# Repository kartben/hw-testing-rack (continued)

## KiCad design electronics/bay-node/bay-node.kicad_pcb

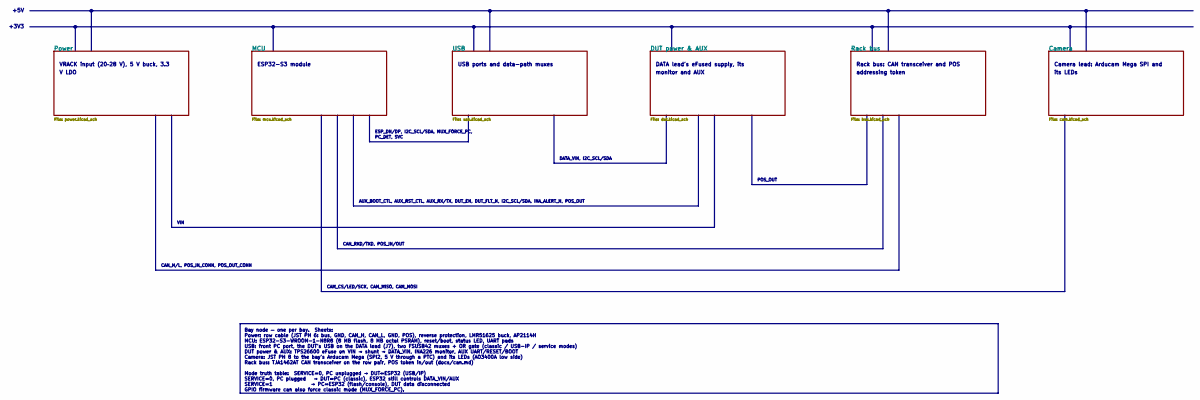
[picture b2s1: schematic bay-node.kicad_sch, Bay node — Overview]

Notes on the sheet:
VRACK input (20–28 V), 5 V buck, 3.3
V LDO
ESP32-S3 module
USB ports and data-path muxes
DATA lead's eFused supply, its
monitor and AUX
Rack bus: CAN transceiver and POS
addressing token
Camera lead: Arducam Mega SPI and
its LEDs
+3V3
+5V
ESP_DN/DP, I2C_SCL/SDA, MUX_FORCE_PC,
PC_DET, SVC
DATA_VIN, I2C_SCL/SDA
POS_OUT
AUX_BOOT_CTL, AUX_RST_CTL, AUX_RX/TX, DUT_EN, DUT_FLT_N, I2C_SCL/SDA, INA_ALERT_N, POS_OUT
VIN
CAN_RXD/TXD, POS_IN/OUT
CAN_H/L, POS_IN_CONN, POS_OUT_CONN
CAM_CS/LED/SCK, CAM_MISO, CAM_MOSI
Bay node — one per bay. Sheets: Power: row cable (JST PH 6: bus, GND, CAN_H, CAN_L, GND, POS), reverse protection, LMR51625 buck, AP2114H MCU: ESP32-S3-WROOM-1-N8R8 (8 MB flash, 8 MB octal PSRAM), reset/boot, status LED, UART pads USB: front PC port, the DUT's USB on the DATA lead (J7), two FSUSB42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

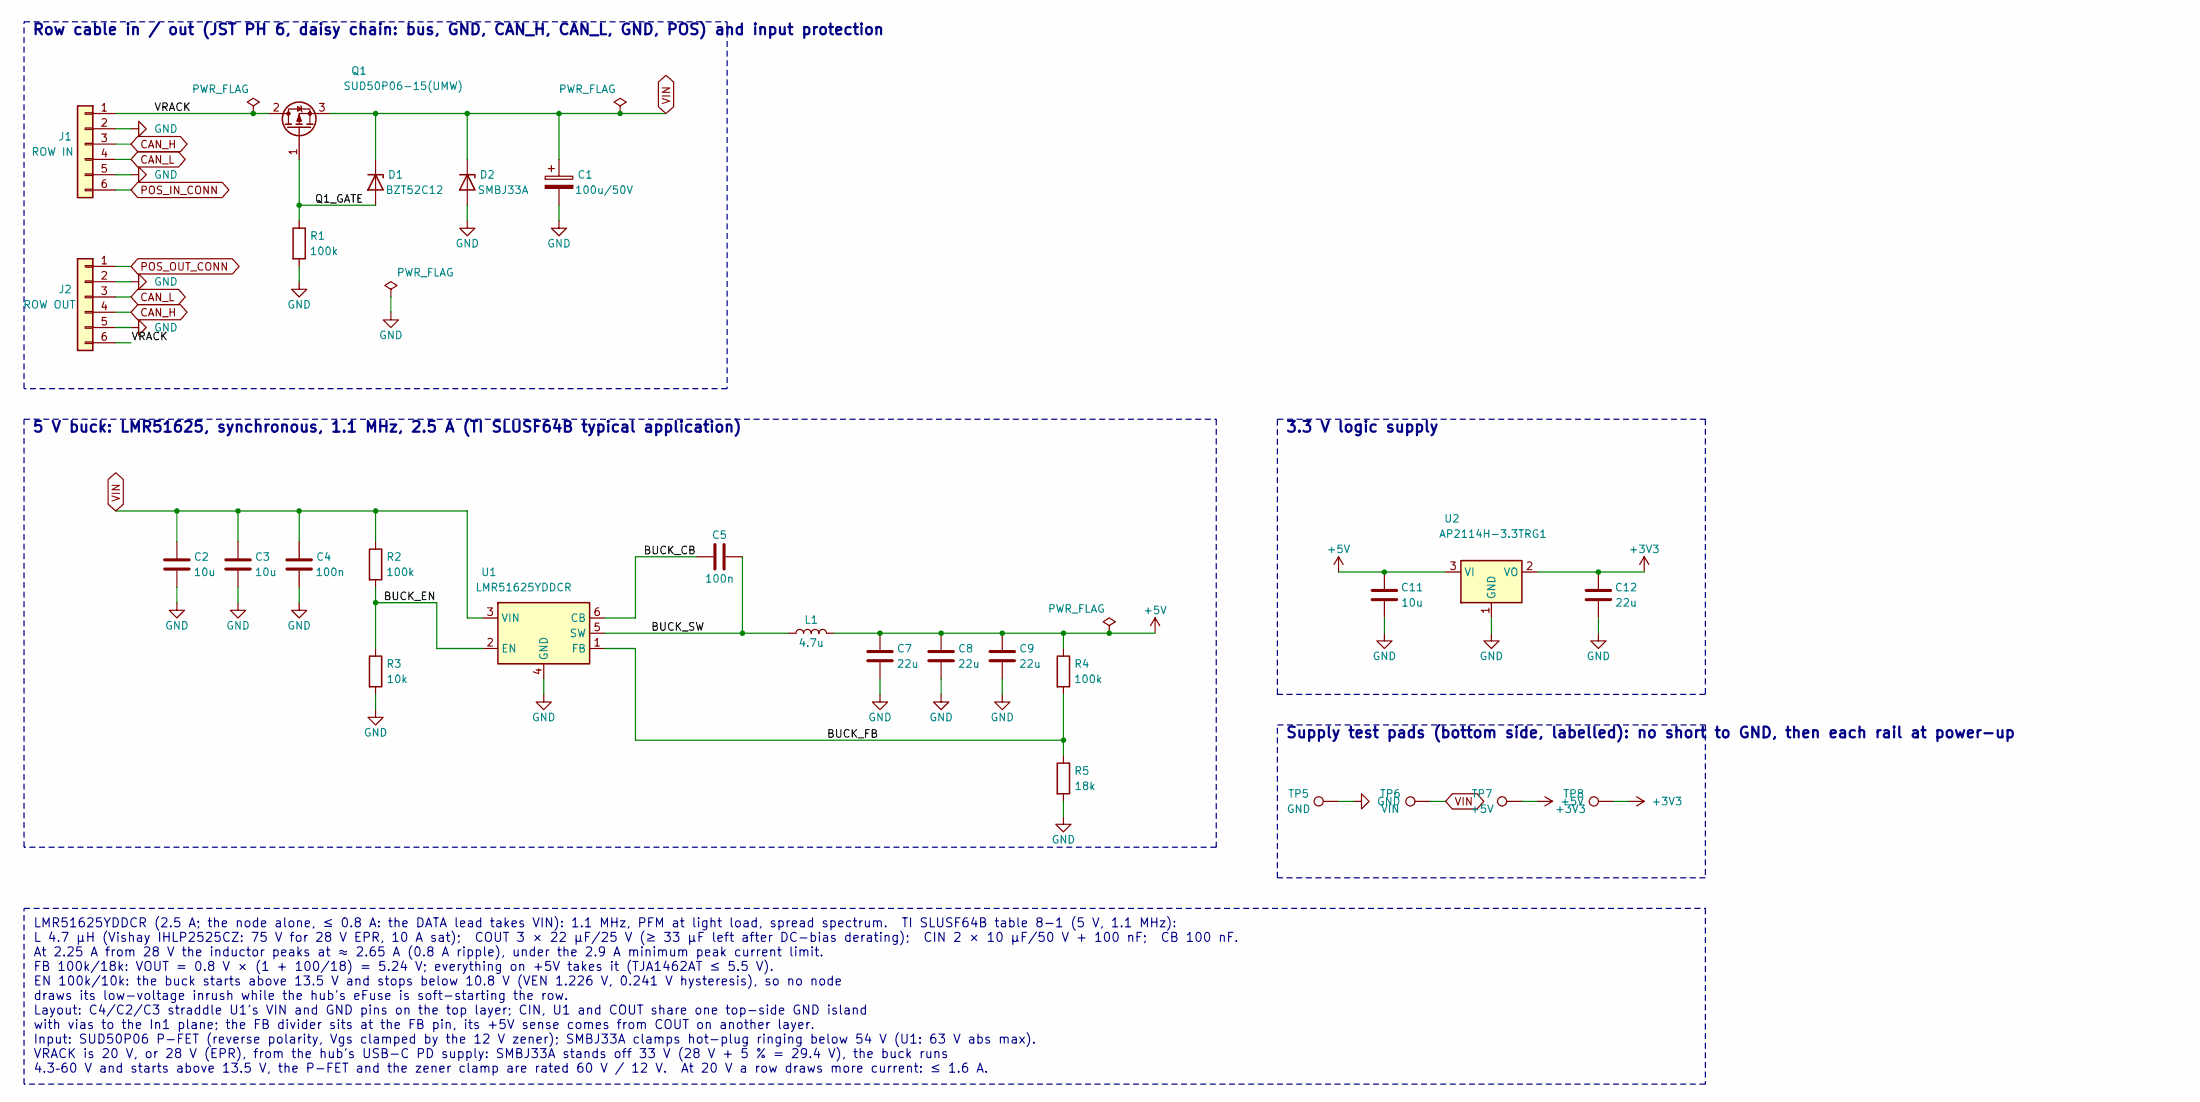
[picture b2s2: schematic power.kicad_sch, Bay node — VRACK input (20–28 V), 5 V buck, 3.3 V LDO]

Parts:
C1: 100u/50V; CP_Elec_8x10; MPN RVT1H101M0810; LCSC C3352
C2, C3: 10u; C_1206_3216Metric; MPN CL31A106KBHNNNE; LCSC C13585
C4, C5: 100n; C_0603_1608Metric; MPN CC0603KRX7R9BB104; LCSC C14663
C7, C8, C9, C12: 22u; C_1206_3216Metric; MPN CL31A226KAHNNNE; LCSC C12891
C11: 10u; C_0805_2012Metric; MPN CL21A106KAYNNNE; LCSC C15850
D1: BZT52C12; D_SOD-123; MPN BZT52C12; LCSC C43491
D2: SMBJ33A; D_SMB; MPN SMBJ33A; LCSC C78419
J1: ROW IN; JST_PH_S6B-PH-SM4-TB_1x06-1MP_P2.00mm_Horizontal; MPN S6B-PH-SM4-TB(LF)(SN); LCSC C265405
J2: ROW OUT; JST_PH_S6B-PH-SM4-TB_1x06-1MP_P2.00mm_Horizontal; MPN S6B-PH-SM4-TB(LF)(SN); LCSC C265405
L1: 4.7u; L_Changjiang_FXL0630; MPN IHLP2525CZEK4R7M01; LCSC C48009678
Q1: SUD50P06-15(UMW); TO-252-2; MPN SUD50P06-15(UMW); LCSC C7503186
R1, R2, R4: 100k; R_0603_1608Metric; MPN 0603WAF1003T5E; LCSC C25803
R3: 10k; R_0603_1608Metric; MPN 0603WAF1002T5E; LCSC C25804
R5: 18k; R_0603_1608Metric; MPN 0603WAF1802T5E; LCSC C25810
TP5: GND; TestPoint_Pad_D1.5mm; MPN test pad
TP6: VIN; TestPoint_Pad_D1.5mm; MPN test pad
TP7: +5V; TestPoint_Pad_D1.5mm; MPN test pad
TP8: +3V3; TestPoint_Pad_D1.5mm; MPN test pad
U1: LMR51625YDDCR; TSOT-23-6; MPN LMR51625YDDCR; LCSC C44991044
U2: AP2114H-3.3TRG1; SOT-223-3_TabPin2; MPN AP2114H-3.3TRG1; LCSC C150716

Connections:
+3V3: C12.1, TP8.1, U2.2 (VO); also elsewhere on the board
+5V: C7.1, C8.1, C9.1, C11.1, L1.2, R4.1, TP7.1, U2.3 (VI); also elsewhere on the board
/Power/BUCK_CB: C5.1, U1.6 (CB)
/Power/BUCK_EN: R2.2, R3.1, U1.2 (EN)
/Power/BUCK_FB: R4.2, R5.1, U1.1 (FB)
/Power/BUCK_SW: C5.2, L1.1, U1.5 (SW)
/Power/Q1_GATE: D1.2 (A), Q1.1 (G), R1.1
/Power/VRACK: J1.1, J2.6, Q1.2 (D)
CAN_H: J1.3, J2.4; also elsewhere on the board
CAN_L: J1.4, J2.3; also elsewhere on the board
GND: C1.2, C2.2, C3.2, C4.2, C7.2, C8.2, C9.2, C11.2, C12.2, D2.2 (A), J1.2, J1.5, J2.2, J2.5, R1.2, R3.2, R5.2, TP5.1, U1.4 (GND), U2.1 (GND); also elsewhere on the board
POS_IN_CONN: J1.6; also elsewhere on the board
POS_OUT_CONN: J2.1; also elsewhere on the board
VIN: C1.1, C2.1, C3.1, C4.1, D1.1 (K), D2.1 (K), Q1.3 (S), R2.1, TP6.1, U1.3 (VIN); also elsewhere on the board

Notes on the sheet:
Row cable in / out (JST PH 6, daisy chain: bus, GND, CAN_H, CAN_L, GND, POS) and input protection
5 V buck: LMR51625, synchronous, 1.1 MHz, 2.5 A (TI SLUSF64B typical application)
3.3 V logic supply
Supply test pads (bottom side, labelled): no short to GND, then each rail at power-up
LMR51625YDDCR (2.5 A; the node alone, ≤ 0.8 A: the DATA lead takes VIN): 1.1 MHz, PFM at light load, spread spectrum. TI SLUSF64B table 8-1 (5 V, 1.1 MHz): L 4.7 µH (Vishay IHLP2525CZ: 75 V for 28 V EPR, 10 A sat); COUT 3 × 22 µF/25 V (≥ 33 µF left after DC-bias derating); CIN 2 × 10 µF/50 V + 100 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

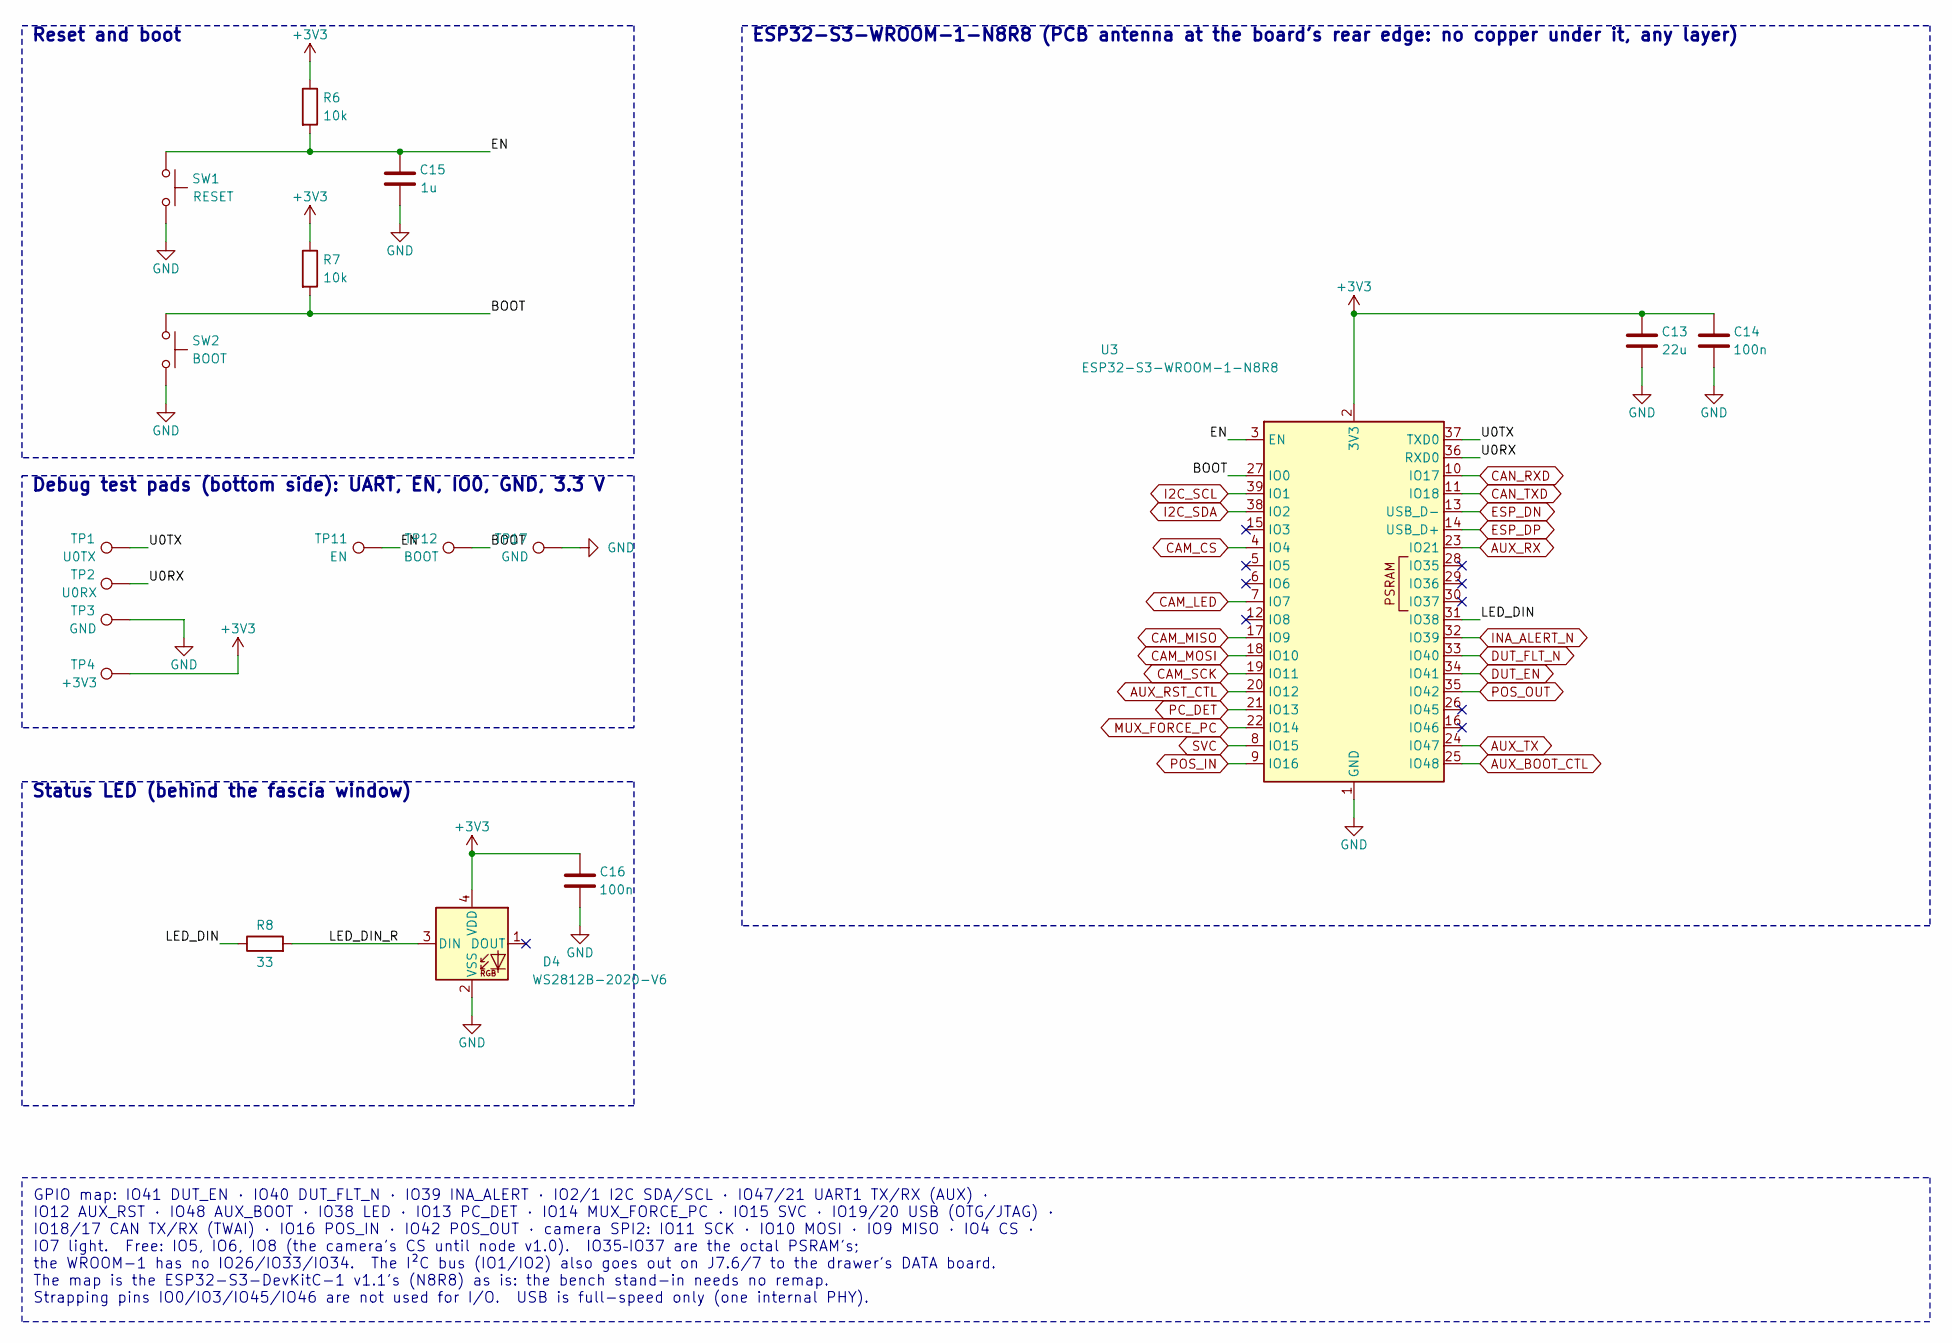
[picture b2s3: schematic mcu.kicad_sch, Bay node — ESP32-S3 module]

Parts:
C13: 22u; C_1206_3216Metric; MPN CL31A226KAHNNNE; LCSC C12891
C14, C16: 100n; C_0603_1608Metric; MPN CC0603KRX7R9BB104; LCSC C14663
C15: 1u; C_0603_1608Metric; MPN CL10A105KB8NNNC; LCSC C15849
D4: WS2812B-2020-V6; LED_WS2812B-2020_PLCC4_2.0x2.0mm; MPN WS2812B-2020-V6; LCSC C52917434
R6, R7: 10k; R_0603_1608Metric; MPN 0603WAF1002T5E; LCSC C25804
R8: 33; R_0603_1608Metric; MPN 0603WAF330JT5E; LCSC C23140
SW1: RESET; SW_Push_1P1T_XKB_TS-1187A; MPN TS-1187A-B-A-B; LCSC C318884
SW2: BOOT; SW_Push_1P1T_XKB_TS-1187A; MPN TS-1187A-B-A-B; LCSC C318884
TP1: U0TX; TestPoint_Pad_D1.5mm; MPN test pad
TP2: U0RX; TestPoint_Pad_D1.5mm; MPN test pad
TP3, TP17: GND; TestPoint_Pad_D1.5mm; MPN test pad
TP4: +3V3; TestPoint_Pad_D1.5mm; MPN test pad
TP11: EN; TestPoint_Pad_D1.0mm; MPN test pad
TP12: BOOT; TestPoint_Pad_D1.0mm; MPN test pad
U3: ESP32-S3-WROOM-1-N8R8; ESP32-S3-WROOM-1_NoEPVias; MPN ESP32-S3-WROOM-1-N8R8; LCSC C2913201

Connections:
+3V3: C13.1, C14.1, C16.1, D4.4 (VDD), R6.1, R7.1, TP4.1, U3.2 (3V3); also elsewhere on the board
/MCU/BOOT: R7.2, SW2.1, TP12.1, U3.27 (IO0)
/MCU/EN: C15.1, R6.2, SW1.1, TP11.1, U3.3 (EN)
/MCU/LED_DIN: R8.1, U3.31 (IO38)
/MCU/LED_DIN_R: D4.3 (DIN), R8.2
/MCU/U0RX: TP2.1, U3.36 (RXD0)
/MCU/U0TX: TP1.1, U3.37 (TXD0)
AUX_BOOT_CTL: U3.25 (IO48); also elsewhere on the board
AUX_RST_CTL: U3.20 (IO12); also elsewhere on the board
AUX_RX: U3.23 (IO21); also elsewhere on the board
AUX_TX: U3.24 (IO47); also elsewhere on the board
CAM_CS: U3.4 (IO4); also elsewhere on the board
CAM_LED: U3.7 (IO7); also elsewhere on the board
CAM_MISO: U3.17 (IO9); also elsewhere on the board
CAM_MOSI: U3.18 (IO10); also elsewhere on the board
CAM_SCK: U3.19 (IO11); also elsewhere on the board
CAN_RXD: U3.10 (IO17); also elsewhere on the board
CAN_TXD: U3.11 (IO18); also elsewhere on the board
DUT_EN: U3.34 (IO41); also elsewhere on the board
DUT_FLT_N: U3.33 (IO40); also elsewhere on the board
ESP_DN: U3.13 (USB_D-); also elsewhere on the board
ESP_DP: U3.14 (USB_D+); also elsewhere on the board
GND: C13.2, C14.2, C15.2, C16.2, D4.2 (VSS), SW1.2, SW2.2, TP3.1, TP17.1, U3.1 (GND), U3.40 (GND), U3.41 (GND); also elsewhere on the board
I2C_SCL: U3.39 (IO1); also elsewhere on the board
I2C_SDA: U3.38 (IO2); also elsewhere on the board
INA_ALERT_N: U3.32 (IO39); also elsewhere on the board
MUX_FORCE_PC: U3.22 (IO14); also elsewhere on the board
PC_DET: U3.21 (IO13); also elsewhere on the board
POS_IN: U3.9 (IO16); also elsewhere on the board
POS_OUT: U3.35 (IO42); also elsewhere on the board
SVC: U3.8 (IO15); also elsewhere on the board

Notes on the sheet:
Reset and boot
Debug test pads (bottom side): UART, EN, IO0, GND, 3.3 V
ESP32-S3-WROOM-1-N8R8 (PCB antenna at the board's rear edge: no copper under it, any layer)
Status LED (behind the fascia window)
GPIO map: IO41 DUT_EN · IO40 DUT_FLT_N · IO39 INA_ALERT · IO2/1 I2C SDA/SCL · IO47/21 UART1 TX/RX (AUX) · IO12 AUX_RST · IO48 AUX_BOOT · IO38 LED · IO13 PC_DET · IO14 MUX_FORCE_PC · IO15 SVC · IO19/20 USB (OTG/JTAG) · IO18/17 CAN TX/RX (TWAI) · IO16 POS_IN · IO42 POS_OUT · camera SPI2: IO11 SCK · I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

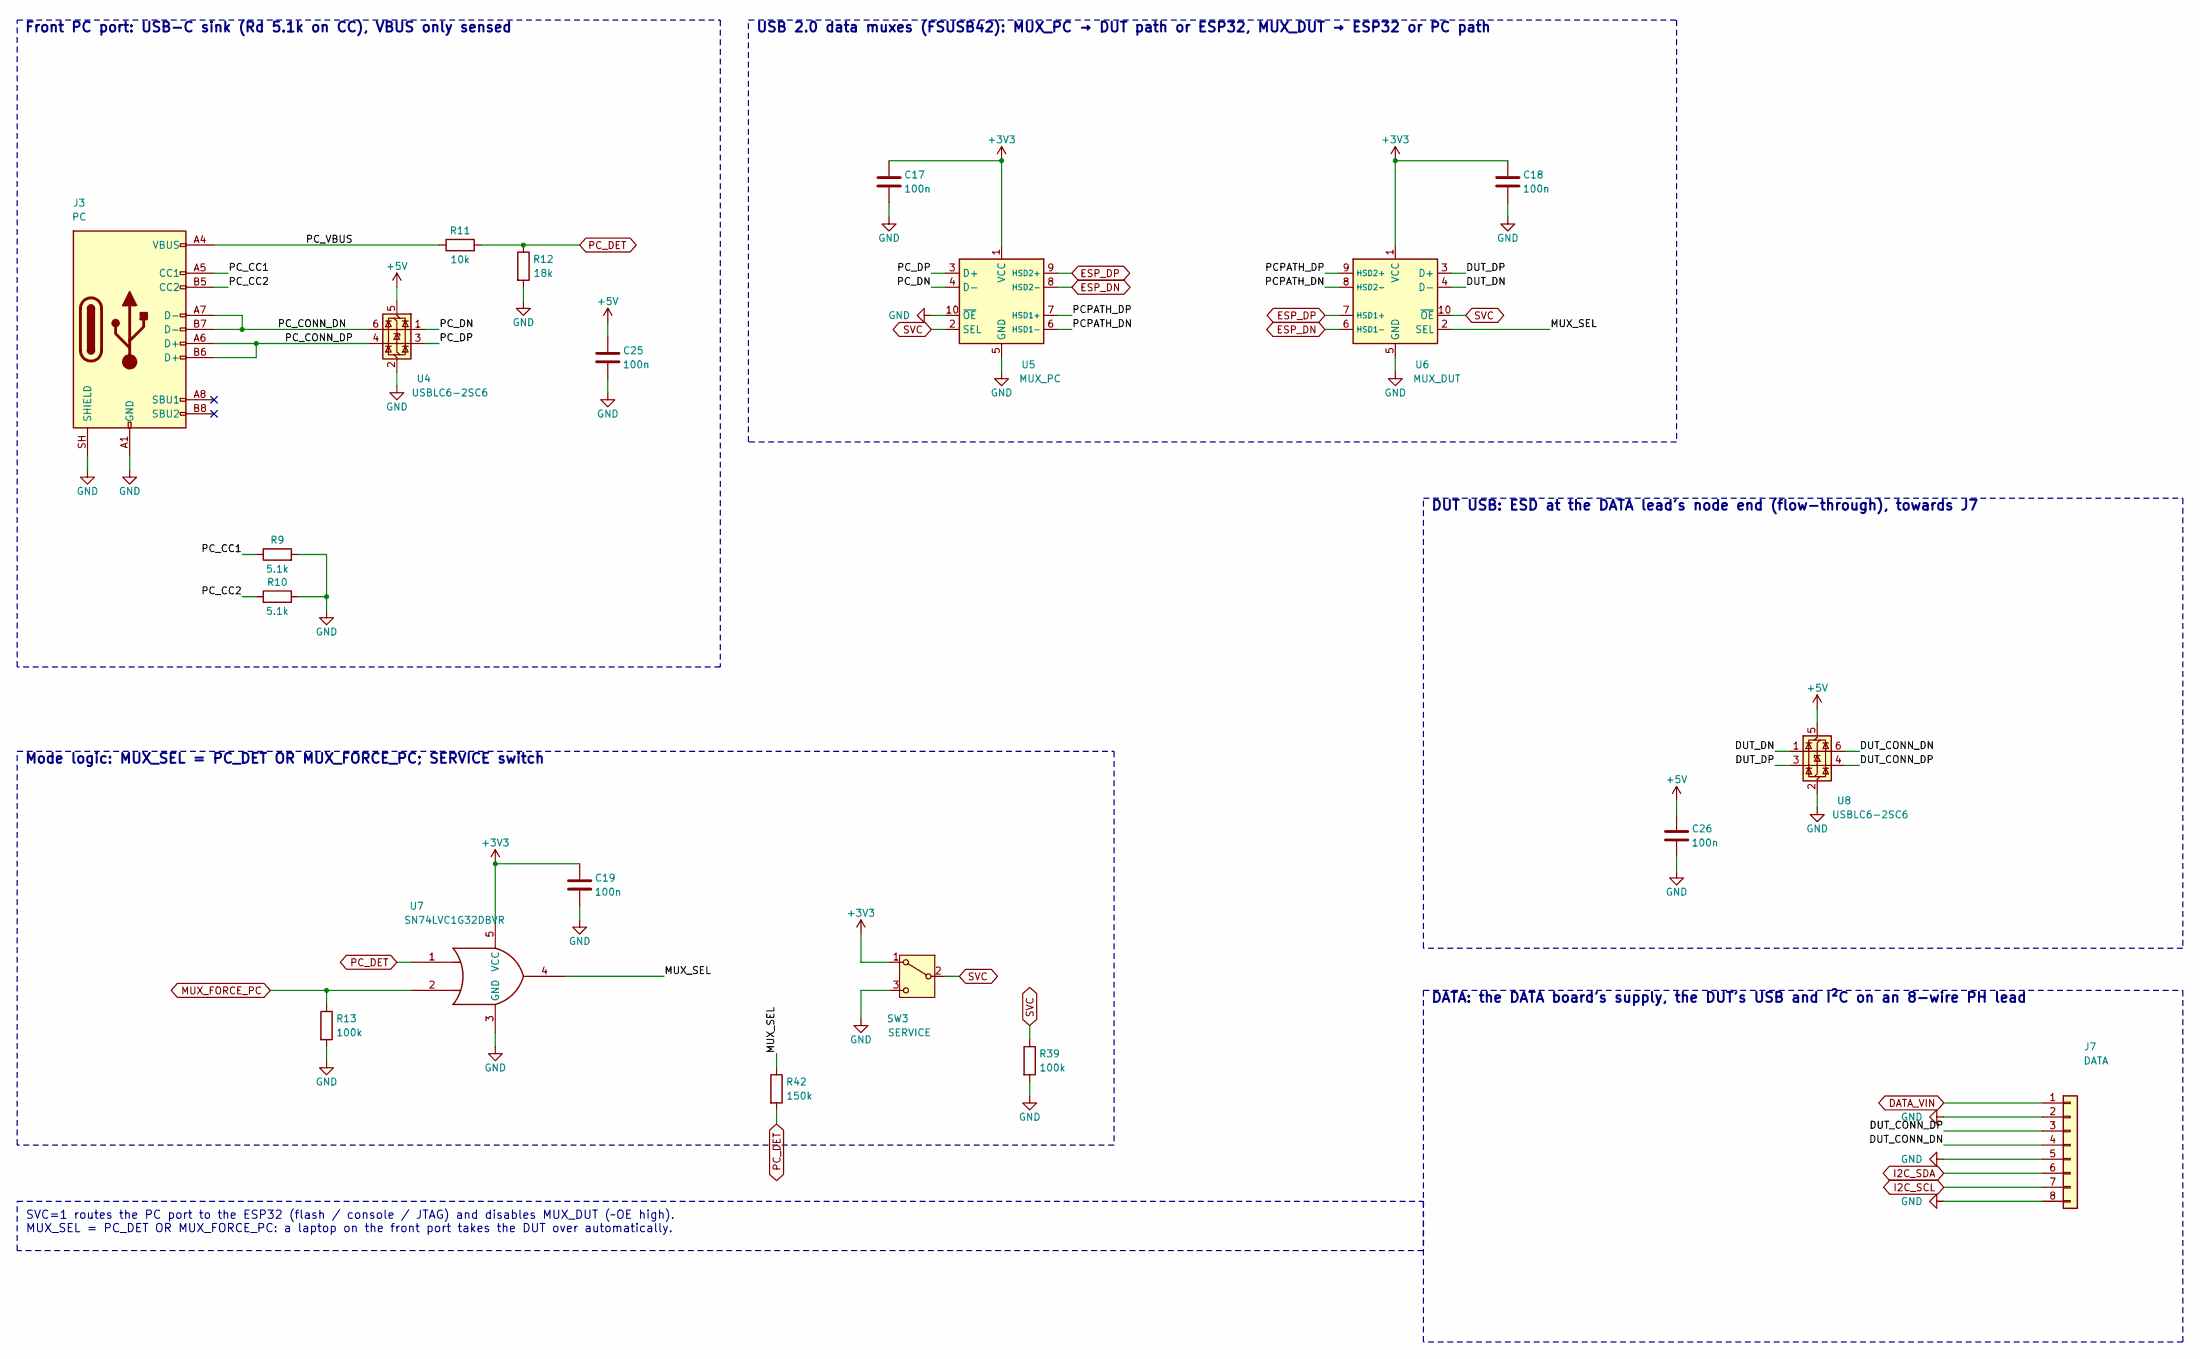
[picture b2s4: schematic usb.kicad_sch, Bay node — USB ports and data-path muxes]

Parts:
C17, C18, C19, C25, C26: 100n; C_0603_1608Metric; MPN CC0603KRX7R9BB104; LCSC C14663
J3: PC; USB_C_Receptacle_GCT_USB4105-xx-A_16P_TopMnt_Horizontal; MPN USB4105-GF-A-120; LCSC C5184243
J7: DATA; JST_PH_S8B-PH-SM4-TB_1x08-1MP_P2.00mm_Horizontal; MPN S8B-PH-SM4-TB(LF)(SN); LCSC C265121
R9, R10: 5.1k; R_0603_1608Metric; MPN 0603WAF5101T5E; LCSC C23186
R11: 10k; R_0603_1608Metric; MPN 0603WAF1002T5E; LCSC C25804
R12: 18k; R_0603_1608Metric; MPN 0603WAF1802T5E; LCSC C25810
R13, R39: 100k; R_0603_1608Metric; MPN 0603WAF1003T5E; LCSC C25803
R42: 150k; R_0603_1608Metric; MPN 0603WAF1503T5E; LCSC C22807
SW3: SERVICE; SW_SPDT_Shouhan_MSK12C02; MPN MSK12C02; LCSC C431540
U4, U8: USBLC6-2SC6; SOT-23-6; MPN USBLC6-2SC6; LCSC C7519
U5: MUX_PC; MSOP-10_3x3mm_P0.5mm; MPN FSUSB42MUX; LCSC C11355
U6: MUX_DUT; MSOP-10_3x3mm_P0.5mm; MPN FSUSB42MUX; LCSC C11355
U7: SN74LVC1G32DBVR; SOT-23-5; MPN SN74LVC1G32DBVR; LCSC C10096

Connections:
+3V3: C17.1, C18.1, C19.1, SW3.1 (A), U5.1 (VCC), U6.1 (VCC), U7.5 (VCC); also elsewhere on the board
+5V: C25.1, C26.1, U4.5 (VBUS), U8.5 (VBUS); also elsewhere on the board
/USB/DUT_CONN_DN: J7.4, U8.6 (I/O1)
/USB/DUT_CONN_DP: J7.3, U8.4 (I/O2)
/USB/DUT_DN: U6.4 (D-), U8.1 (I/O1)
/USB/DUT_DP: U6.3 (D+), U8.3 (I/O2)
/USB/MUX_SEL: R42.1, U6.2 (SEL), U7.4
/USB/PCPATH_DN: U5.6 (HSD1-), U6.8 (HSD2-)
/USB/PCPATH_DP: U5.7 (HSD1+), U6.9 (HSD2+)
/USB/PC_CC1: J3.A5 (CC1), R9.1
/USB/PC_CC2: J3.B5 (CC2), R10.1
/USB/PC_CONN_DN: J3.A7 (D-), J3.B7 (D-), U4.6 (I/O1)
/USB/PC_CONN_DP: J3.A6 (D+), J3.B6 (D+), U4.4 (I/O2)
/USB/PC_DN: U4.1 (I/O1), U5.4 (D-)
/USB/PC_DP: U4.3 (I/O2), U5.3 (D+)
/USB/PC_VBUS: J3.A4 (VBUS), J3.A9 (VBUS), J3.B4 (VBUS), J3.B9 (VBUS), R11.1
DATA_VIN: J7.1; also elsewhere on the board
ESP_DN: U5.8 (HSD2-), U6.6 (HSD1-); also elsewhere on the board
ESP_DP: U5.9 (HSD2+), U6.7 (HSD1+); also elsewhere on the board
GND: C17.2, C18.2, C19.2, C25.2, C26.2, J3.A1 (GND), J3.A12 (GND), J3.B1 (GND), J3.B12 (GND), J3.SH (SHIELD), J7.2, J7.5, J7.8, R9.2, R10.2, R12.2, R13.2, R39.2, SW3.3 (C), U4.2 (GND), U5.5 (GND), U5.10 (~OE), U6.5 (GND), U7.3 (GND), U8.2 (GND); also elsewhere on the board
I2C_SCL: J7.7; also elsewhere on the board
I2C_SDA: J7.6; also elsewhere on the board
MUX_FORCE_PC: R13.1, U7.2; also elsewhere on the board
PC_DET: R11.2, R12.1, R42.2, U7.1; also elsewhere on the board
SVC: R39.1, SW3.2 (B), U5.2 (SEL), U6.10 (~OE); also elsewhere on the board

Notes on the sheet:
Front PC port: USB-C sink (Rd 5.1k on CC), VBUS only sensed
USB 2.0 data muxes (FSUSB42): MUX_PC → DUT path or ESP32, MUX_DUT → ESP32 or PC path
DUT USB: ESD at the DATA lead's node end (flow-through), towards J7
DATA: the DATA board's supply, the DUT's USB and I²C on an 8-wire PH lead
Mode logic: MUX_SEL = PC_DET OR MUX_FORCE_PC; SERVICE switch
SVC=1 routes the PC port to the ESP32 (flash / console / JTAG) and disables MUX_DUT (~OE high). MUX_SEL = PC_DET OR MUX_FORCE_PC: a laptop on the front port takes the DUT over automatically.

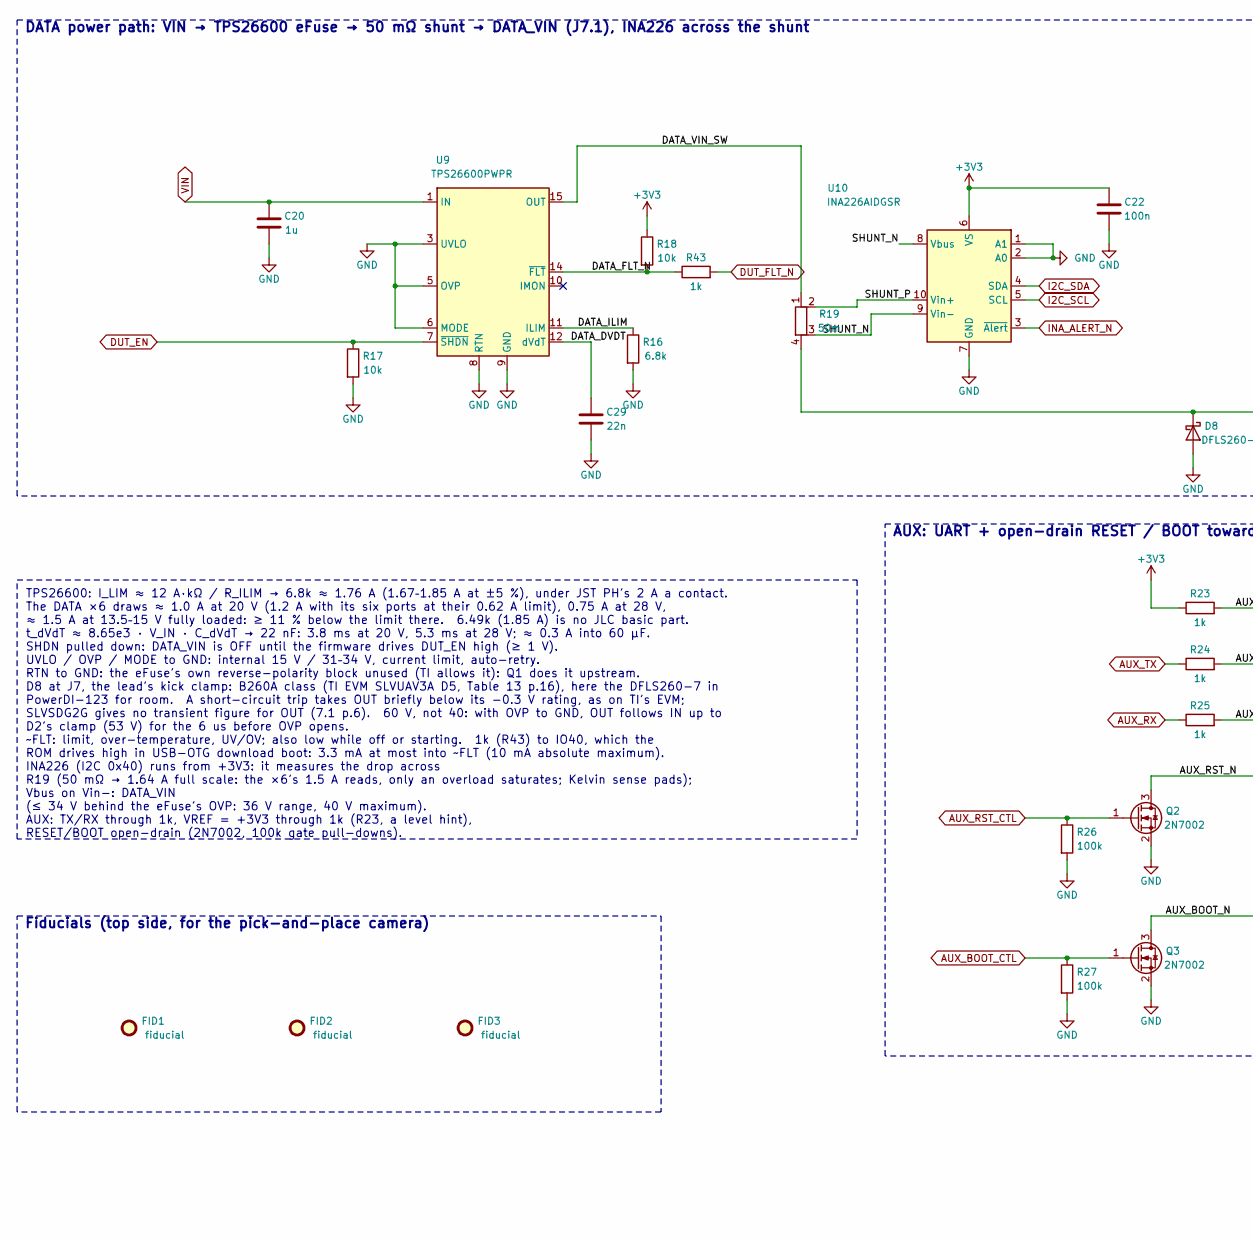
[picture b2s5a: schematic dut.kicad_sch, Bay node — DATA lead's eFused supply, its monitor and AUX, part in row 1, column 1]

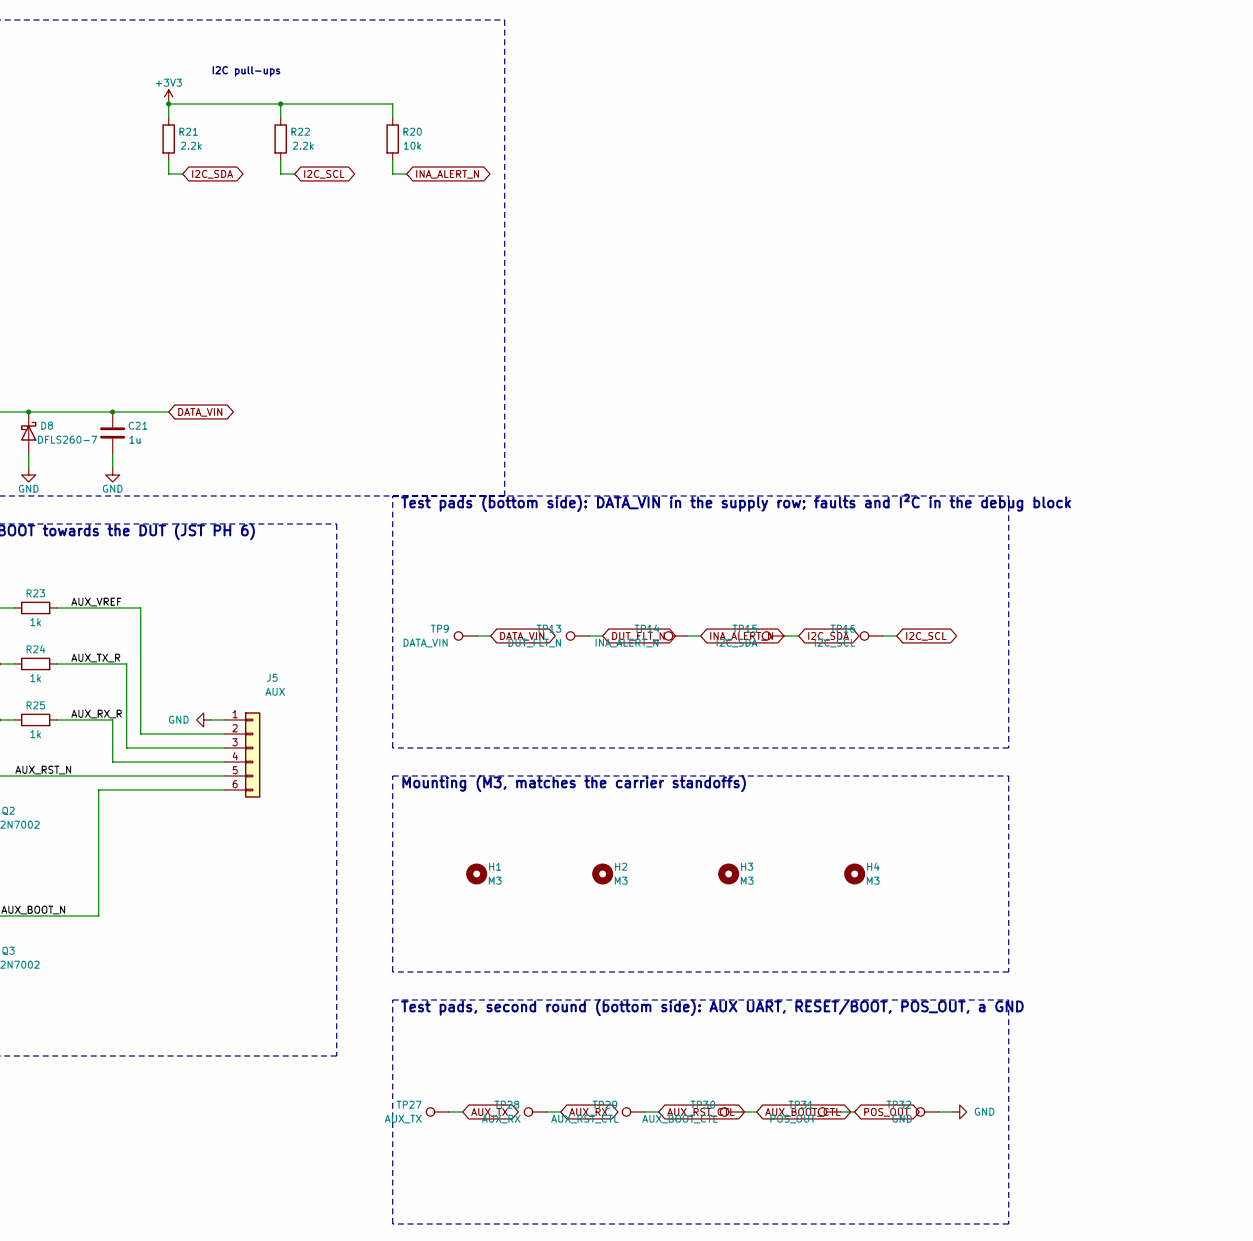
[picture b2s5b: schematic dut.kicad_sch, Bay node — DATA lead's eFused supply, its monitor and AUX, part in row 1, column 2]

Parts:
C20, C21: 1u; C_0805_2012Metric; MPN CL21B105KBFNNNE; LCSC C28323
C22: 100n; C_0603_1608Metric; MPN CC0603KRX7R9BB104; LCSC C14663
C29: 22n; C_0603_1608Metric; MPN CL10B223KB8NNNC; LCSC C21122
D8: DFLS260-7; D_PowerDI-123; MPN DFLS260-7; LCSC C209346
FID1, FID2, FID3: fiducial; Fiducial_1mm_Mask2mm; MPN fiducial
H1, H2, H3, H4: M3; MountingHole_3.2mm_M3; MPN M3 mounting hole
J5: AUX; JST_PH_S6B-PH-SM4-TB_1x06-1MP_P2.00mm_Horizontal; MPN S6B-PH-SM4-TB(LF)(SN); LCSC C265405
Q2, Q3: 2N7002; SOT-23; MPN 2N7002; LCSC C8545
R16: 6.8k; R_0603_1608Metric; MPN 0603WAF6801T5E; LCSC C23212
R17, R18, R20: 10k; R_0603_1608Metric; MPN 0603WAF1002T5E; LCSC C25804
R19: 50m; R_1206_3216Metric_Kelvin; MPN HoLR1206-1W-50mR-1%-75ppm; LCSC C601102
R21, R22: 2.2k; R_0603_1608Metric; MPN 0603WAF2201T5E; LCSC C4190
R23, R24, R25, R43: 1k; R_0603_1608Metric; MPN 0603WAF1001T5E; LCSC C21190
R26, R27: 100k; R_0603_1608Metric; MPN 0603WAF1003T5E; LCSC C25803
TP9: DATA_VIN; TestPoint_Pad_D1.5mm; MPN test pad
TP13: DUT_FLT_N; TestPoint_Pad_D1.0mm; MPN test pad
TP14: INA_ALERT_N; TestPoint_Pad_D1.0mm; MPN test pad
TP15: I2C_SDA; TestPoint_Pad_D1.0mm; MPN test pad
TP16: I2C_SCL; TestPoint_Pad_D1.0mm; MPN test pad
TP27: AUX_TX; TestPoint_Pad_D1.0mm; MPN test pad
TP28: AUX_RX; TestPoint_Pad_D1.0mm; MPN test pad
TP29: AUX_RST_CTL; TestPoint_Pad_D1.0mm; MPN test pad
TP30: AUX_BOOT_CTL; TestPoint_Pad_D1.0mm; MPN test pad
TP31: POS_OUT; TestPoint_Pad_D1.0mm; MPN test pad
TP32: GND; TestPoint_Pad_D1.5mm; MPN test pad
U9: TPS26600PWPR; HTSSOP-16-1EP_4.4x5mm_P0.65mm_EP3.4x5mm_Mask2.66x2.46mm; MPN TPS26600PWPR; LCSC C544399
U10: INA226AIDGSR; TSSOP-10_3x3mm_P0.5mm; MPN INA226AIDGSR; LCSC C49851

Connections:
+3V3: C22.1, R18.1, R20.1, R21.1, R22.1, R23.1, U10.6 (VS); also elsewhere on the board
/DUT power & AUX/AUX_BOOT_N: J5.6, Q3.3 (D)
/DUT power & AUX/AUX_RST_N: J5.5, Q2.3 (D)
/DUT power & AUX/AUX_RX_R: J5.4, R25.2
/DUT power & AUX/AUX_TX_R: J5.3, R24.2
/DUT power & AUX/AUX_VREF: J5.2, R23.2
/DUT power & AUX/DATA_DVDT: C29.1, U9.12 (dVdT)
/DUT power & AUX/DATA_FLT_N: R18.2, R43.1, U9.14 (~FLT)
/DUT power & AUX/DATA_ILIM: R16.1, U9.11 (ILIM)
/DUT power & AUX/DATA_VIN_SW: R19.1, U9.15 (OUT), U9.16 (OUT)
/DUT power & AUX/SHUNT_N: R19.3, U10.8 (Vbus), U10.9 (Vin-)
/DUT power & AUX/SHUNT_P: R19.2, U10.10 (Vin+)
AUX_BOOT_CTL: Q3.1 (G), R27.1, TP30.1; also elsewhere on the board
AUX_RST_CTL: Q2.1 (G), R26.1, TP29.1; also elsewhere on the board
AUX_RX: R25.1, TP28.1; also elsewhere on the board
AUX_TX: R24.1, TP27.1; also elsewhere on the board
DATA_VIN: C21.1, D8.1 (K), R19.4, TP9.1; also elsewhere on the board
DUT_EN: R17.1, U9.7 (~SHDN); also elsewhere on the board
DUT_FLT_N: R43.2, TP13.1; also elsewhere on the board
GND: C20.2, C21.2, C22.2, C29.2, D8.2 (A), J5.1, Q2.2 (S), Q3.2 (S), R16.2, R17.2, R26.2, R27.2, TP32.1, U9.3 (UVLO), U9.5 (OVP), U9.6 (MODE), U9.8 (RTN), U9.9 (GND), U9.17 (RTN), U10.1 (A1), U10.2 (A0), U10.7 (GND); also elsewhere on the board
I2C_SCL: R22.2, TP16.1, U10.5 (SCL); also elsewhere on the board
I2C_SDA: R21.2, TP15.1, U10.4 (SDA); also elsewhere on the board
INA_ALERT_N: R20.2, TP14.1, U10.3 (~Alert); also elsewhere on the board
POS_OUT: TP31.1; also elsewhere on the board
VIN: C20.1, U9.1 (IN), U9.2 (IN); also elsewhere on the board

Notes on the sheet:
DATA power path: VIN → TPS26600 eFuse → 50 mΩ shunt → DATA_VIN (J7.1), INA226 across the shunt
AUX: UART + open-drain RESET / BOOT towards the DUT (JST PH 6)
Test pads (bottom side): DATA_VIN in the supply row; faults and I²C in the debug block
Mounting (M3, matches the carrier standoffs)
Fiducials (top side, for the pick-and-place camera)
Test pads, second round (bottom side): AUX UART, RESET/BOOT, POS_OUT, a GND
I2C pull-ups
TPS26600: I_LIM ≈ 12 A·kΩ / R_ILIM → 6.8k ≈ 1.76 A (1.67–1.85 A at ±5 %), under JST PH's 2 A a contact. The DATA ×6 draws ≈ 1.0 A at 20 V (1.2 A with its six ports at their 0.62 A limit), 0.75 A at 28 V, ≈ 1.5 A at 13.5–15 V fully loaded: ≥ 11 % below the limit there. 6.49k (1.85 A) is no JLC basic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

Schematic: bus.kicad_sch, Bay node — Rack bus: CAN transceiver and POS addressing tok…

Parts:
C23, C24: 100n; C_0603_1608Metric; MPN CC0603KRX7R9BB104; LCSC C14663
D5: PESD2CAN; SOT-23; MPN PESD2CAN,215; LCSC C75176
D6, D7: BAT54S; SOT-23; MPN BAT54S; LCSC C7420333
R28, R30: 10k; R_0603_1608Metric; MPN 0603WAF1002T5E; LCSC C25804
R29: 150k; R_0603_1608Metric; MPN 0603WAF1503T5E; LCSC C22807
TP23: CAN_TXD; TestPoint_Pad_D1.0mm; MPN test pad
TP24: CAN_RXD; TestPoint_Pad_D1.0mm; MPN test pad
TP25: POS_IN; TestPoint_Pad_D1.0mm; MPN test pad
TP26: GND; TestPoint_Pad_D1.5mm; MPN test pad
U11: TJA1462AT; SOIC-8_3.9x4.9mm_P1.27mm; MPN TJA1462AT/0Z; LCSC C3234095

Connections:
+3V3: C24.1, D6.2 (K), D7.2 (K), U11.5 (Vio); also elsewhere on the board
+5V: C23.1, U11.3 (VDD); also elsewhere on the board
CAN_H: D5.1 (K), U11.7 (CANH); also elsewhere on the board
CAN_L: D5.2 (K), U11.6 (CANL); also elsewhere on the board
CAN_RXD: TP24.1, U11.4 (RXD); also elsewhere on the board
CAN_TXD: TP23.1, U11.1 (TXD); also elsewhere on the board
GND: C23.2, C24.2, D5.3 (A), D6.1 (A), D7.1 (A), R29.2, TP26.1, U11.2 (VSS), U11.8 (STBY); also elsewhere on the board
POS_IN: D6.3 (COM), R28.2, R29.1, TP25.1; also elsewhere on the board
POS_IN_CONN: R28.1; also elsewhere on the board
POS_OUT: D7.3 (COM), R30.1; also elsewhere on the board
POS_OUT_CONN: R30.2; also elsewhere on the board

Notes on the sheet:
CAN: TJA1462AT on the row pair (J1.3/4 ↔ J2.4/3, Power sheet); stub ≤ 20 mm, no termination
POS token: in from J1.6, out to J2.1; 10k series + BAT54S clamp on each (VRACK on it costs ≈ 2.5 mA at 28 V)
Test pads, second round (bottom side): CAN TXD/RXD, POS_IN, a GND
STB low: always in normal mode (TXD dominant time-out guards the bus).
CAN (docs/can.md): one bus for the rack, a star from the hub; both terminations sit in the hub. 250 kbit/s (125 kbit/s fallback). TJA1462AT (SIC): VCC 5 V, VIO 3.3 V, bus pins −36/+40 V, passive unpowered. POS: active-high 3.3 V token. From reset the node holds POS_OUT low; when POS_IN goes high an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

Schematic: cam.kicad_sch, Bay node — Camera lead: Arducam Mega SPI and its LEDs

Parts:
C27, C28: 100n; C_0603_1608Metric; MPN CC0603KRX7R9BB104; LCSC C14663
F1: 0.75A; Fuse_1206_3216Metric; MPN SMD1206P075TF; LCSC C20987
J6: CAM; JST_PH_B8B-PH-SM4-TB_1x08-1MP_P2.00mm_Vertical; MPN B8B-PH-SM4-TB(LF)(SN); LCSC C495548
Q4: AO3400A; SOT-23; MPN AO3400A; LCSC C20917
R31, R32, R33, R34: 33; R_0603_1608Metric; MPN 0603WAF330JT5E; LCSC C23140
R35: 680; R_0603_1608Metric; MPN 0603WAF6800T5E; LCSC C23228; not fitted
R36: 100k; R_0603_1608Metric; MPN 0603WAF1003T5E; LCSC C25803
R37: 10k; R_0603_1608Metric; MPN 0603WAF1002T5E; LCSC C25804
TP10: CAM_5V; TestPoint_Pad_D1.5mm; MPN test pad
TP18: CAM_SCK_C; TestPoint_Pad_D1.0mm; MPN test pad
TP19: CAM_MOSI_P; TestPoint_Pad_D1.0mm; MPN test pad
TP20: CAM_MISO_P; TestPoint_Pad_D1.0mm; MPN test pad
TP21: CAM_CS_P; TestPoint_Pad_D1.0mm; MPN test pad
TP22: GND; TestPoint_Pad_D1.5mm; MPN test pad
U12, U13: USBLC6-2SC6; SOT-23-6; MPN USBLC6-2SC6; LCSC C7519

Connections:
+3V3: C28.1, R37.2, U12.5 (VBUS), U13.5 (VBUS); also elsewhere on the board
+5V: F1.1; also elsewhere on the board
/Camera/CAM_5V: C27.1, F1.2, J6.3, TP10.1
/Camera/CAM_CS_C: J6.7, U13.4 (I/O2)
/Camera/CAM_CS_P: R34.2, TP21.1, U13.3 (I/O2)
/Camera/CAM_MISO_C: J6.5, U13.6 (I/O1)
/Camera/CAM_MISO_P: R33.1, TP20.1, U13.1 (I/O1)
/Camera/CAM_MOSI_C: J6.4, U12.4 (I/O2)
/Camera/CAM_MOSI_P: R32.2, TP19.1, U12.3 (I/O2)
/Camera/CAM_SCK_C: J6.2, TP18.1, U12.6 (I/O1)
/Camera/CAM_SCK_P: R31.2, U12.1 (I/O1)
/Camera/LED_K: J6.6, Q4.3 (D)
CAM_CS: R34.1, R37.1; also elsewhere on the board
CAM_LED: Q4.1 (G), R36.1; also elsewhere on the board
CAM_MISO: R33.2, R35.1; also elsewhere on the board
CAM_MOSI: R32.1; also elsewhere on the board
CAM_SCK: R31.1; also elsewhere on the board
GND: C27.2, C28.2, J6.1, J6.8, Q4.2 (S), R35.2, R36.2, TP22.1, U12.2 (GND), U13.2 (GND); also elsewhere on the board

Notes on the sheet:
J6: JST PH 8 to the bay's camera pod (Arducam Mega 3MP SPI + white LEDs), ≈ 50 cm
CAM_5V test pad (bottom side, in the supply row)
Test pads, second round (bottom side): the camera SPI and a GND
Lead pinout: 1 GND · 2 SCK · 3 CAM_5V · 4 MOSI · 5 MISO · 6 LED_K (the LEDs' cathode side) · 7 CS · 8 GND. SPI2 through the GPIO matrix, mode 0, 4 MHz (2 MHz fallback): IO11 SCK, IO10 MOSI, IO9 MISO, IO4 CS (10k pull-up: deselected before firmware), IO7 the light (R36 holds it off at boot; LEDC PWM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
